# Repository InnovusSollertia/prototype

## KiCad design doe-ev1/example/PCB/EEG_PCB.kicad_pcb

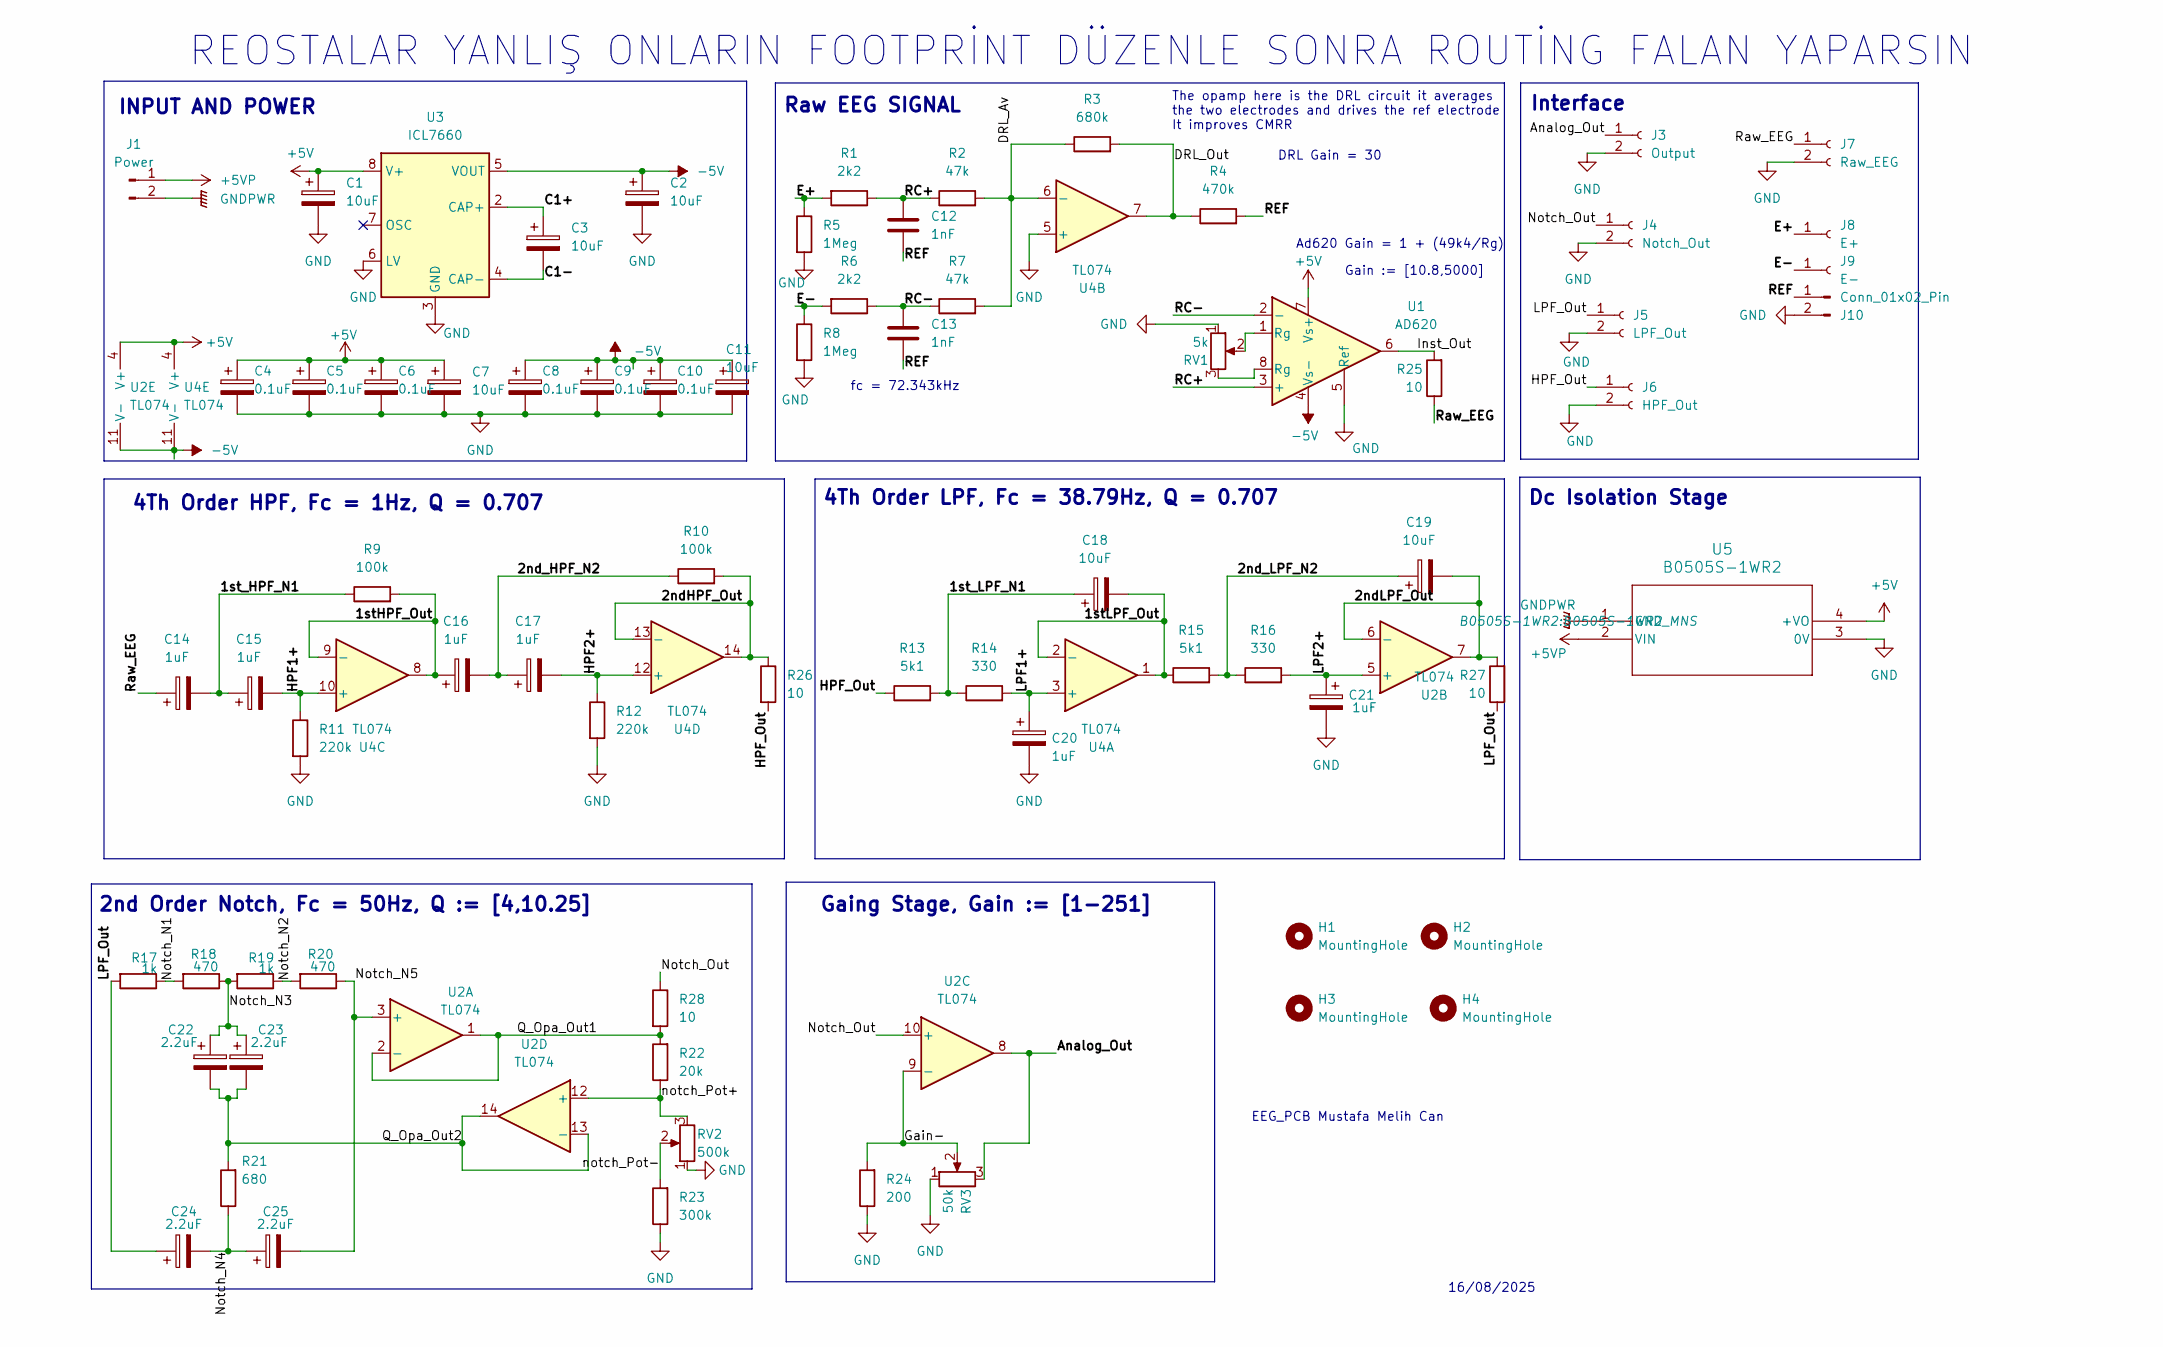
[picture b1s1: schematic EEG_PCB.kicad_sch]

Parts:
C1, C2, C3, C7, C11, C18, C19: 10uF; CP_Radial_D5.0mm_P2.50mm
C4, C5, C6, C8, C9, C10: 0.1uF; CP_Radial_D5.0mm_P2.50mm
C12, C13: 1nF; C_Disc_D4.7mm_W2.5mm_P5.00mm
C14, C15, C16, C17, C20, C21: 1uF; CP_Radial_D5.0mm_P2.50mm
C22, C23, C24, C25: 2.2uF; CP_Radial_D5.0mm_P2.50mm
H1, H2, H3, H4: MountingHole; MountingHole_4.3mm_M4
J1: Power; PinHeader_1x02_P2.54mm_Vertical
J3: Output; PinHeader_1x02_P2.54mm_Vertical
J4: Notch_Out; PinHeader_1x02_P2.54mm_Vertical
J5: LPF_Out; PinHeader_1x02_P2.54mm_Vertical
J6: HPF_Out; PinHeader_1x02_P2.54mm_Vertical
J7: Raw_EEG; PinHeader_1x02_P2.54mm_Vertical
J8: E+; PinHeader_1x01_P2.54mm_Vertical
J9: E-; PinHeader_1x01_P2.54mm_Vertical
J10: Conn_01x02_Pin; PinHeader_1x02_P2.54mm_Vertical
R1, R6: 2k2; R_Axial_DIN0207_L6.3mm_D2.5mm_P10.16mm_Horizontal
R2, R7: 47k; R_Axial_DIN0207_L6.3mm_D2.5mm_P10.16mm_Horizontal
R3: 680k; R_Axial_DIN0207_L6.3mm_D2.5mm_P10.16mm_Horizontal
R4: 470k; R_Axial_DIN0207_L6.3mm_D2.5mm_P10.16mm_Horizontal
R5, R8: 1Meg; R_Axial_DIN0207_L6.3mm_D2.5mm_P10.16mm_Horizontal
R9, R10: 100k; R_Axial_DIN0207_L6.3mm_D2.5mm_P10.16mm_Horizontal
R11, R12: 220k; R_Axial_DIN0207_L6.3mm_D2.5mm_P10.16mm_Horizontal
R13, R15: 5k1; R_Axial_DIN0207_L6.3mm_D2.5mm_P10.16mm_Horizontal
R14, R16: 330; R_Axial_DIN0207_L6.3mm_D2.5mm_P10.16mm_Horizontal
R17, R19: 1k; R_Axial_DIN0207_L6.3mm_D2.5mm_P10.16mm_Horizontal
R18, R20: 470; R_Axial_DIN0207_L6.3mm_D2.5mm_P10.16mm_Horizontal
R21: 680; R_Axial_DIN0207_L6.3mm_D2.5mm_P10.16mm_Horizontal
R22: 20k; R_Axial_DIN0207_L6.3mm_D2.5mm_P10.16mm_Horizontal
R23: 300k; R_Axial_DIN0207_L6.3mm_D2.5mm_P10.16mm_Horizontal
R24: 200; R_Axial_DIN0207_L6.3mm_D2.5mm_P10.16mm_Horizontal
R25, R26, R27, R28: 10; R_Axial_DIN0207_L6.3mm_D2.5mm_P10.16mm_Horizontal
RV1: 5k; Potentiometer_Alps_RK163_Single_Horizontal
RV2: 500k; Potentiometer_Alps_RK163_Single_Horizontal
RV3: 50k; Potentiometer_Alps_RK163_Single_Horizontal
U1: AD620; DIP-8_W7.62mm_LongPads
U2, U4: TL074; DIP-14_W7.62mm_LongPads
U3: ICL7660; DIP-8_W7.62mm_LongPads
U5: B0505S-1WR2; B0505S-1WR2_MNS

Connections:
+5V: C1.1, C4.1, C5.1, C6.1, C7.1, U1.7 (Vs+), U2.4 (V+), U3.8 (V+), U4.4 (V+), U5.4 (+VO)
+5VP: J1.1, U5.2 (VIN)
-5V: C2.1, C8.1, C9.1, C10.1, C11.1, U1.4 (Vs-), U2.11 (V-), U3.5 (VOUT), U4.11 (V-)
/1stHPF_Out: C16.1, R9.2, U4.8, U4.9 (-)
/1stLPF_Out: C18.2, R15.1, U4.1, U4.2 (-)
/1st_HPF_N1: C14.2, C15.1, R9.1
/1st_LPF_N1: C18.1, R13.2, R14.1
/2ndHPF_Out: R10.2, R26.1, U4.13 (-), U4.14
/2ndLPF_Out: C19.2, R27.2, U2.6 (-), U2.7
/2nd_HPF_N2: C16.2, C17.1, R10.1
/2nd_LPF_N2: C19.1, R15.2, R16.1
/Analog_Out: J3.1, RV3.3, U2.8
/C1+: C3.1, U3.2 (CAP+)
/C1-: C3.2, U3.4 (CAP-)
/DRL_Av: R2.2, R3.1, R7.2, U4.6 (-)
/DRL_Out: R3.2, R4.1, U4.7
/E+: J8.1, R1.2, R5.1
/E-: J9.1, R6.2, R8.1
/Gain-: R24.2, RV3.2, U2.9 (-)
/HPF1+: C15.2, R11.1, U4.10 (+)
/HPF2+: C17.2, R12.1, U4.12 (+)
/HPF_Out: J6.1, R13.1, R26.2
/Inst_Out: R25.2, U1.6
/LPF1+: C20.1, R14.2, U4.3 (+)
/LPF2+: C21.1, R16.2, U2.5 (+)
/LPF_Out: C24.1, J5.1, R17.2, R27.1
/Notch_N1: R17.1, R18.2
/Notch_N2: R19.1, R20.2
/Notch_N3: C22.1, C23.1, R18.1, R19.2
/Notch_N4: C24.2, C25.1, R21.1
/Notch_N5: C25.2, R20.1, U2.3 (+)
/Notch_Out: J4.1, R28.1, U2.10 (+)
/Q_Opa_Out1: R22.2, R28.2, U2.1, U2.2 (-)
/Q_Opa_Out2: C22.2, C23.2, R21.2, U2.13 (-), U2.14
/RC+: C12.1, R1.1, R2.1, U1.3 (+)
/RC-: C13.1, R6.1, R7.1, U1.2 (-)
/REF: C12.2, C13.2, J10.1, R4.2
/Raw_EEG: C14.1, J7.1, R25.1
/notch_Pot+: R22.1, RV2.3, U2.12 (+)
/notch_Pot-: R23.2, RV2.2
GND: C1.2, C2.2, C4.2, C5.2, C6.2, C7.2, C8.2, C9.2, C10.2, C11.2, C20.2, C21.2, J3.2, J4.2, J5.2, J6.2, J7.2, J10.2, R5.2, R8.2, R11.2, R12.2, R23.1, R24.1, RV1.1, RV2.1, RV3.1, U1.5 (Ref), U3.3 (GND), U3.6 (LV), U4.5 (+), U5.3 (0V)
GNDPWR: J1.2, U5.1 (GND)
unnamed: RV1.2, U1.1 (Rg)
unnamed: RV1.3, U1.8 (Rg)

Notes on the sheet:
REOSTALAR YANLIŞ ONLARIN FOOTPRİNT DÜZENLE SONRA ROUTİNG FALAN YAPARSIN
fc = 72.343kHz
The opamp here is the DRL circuit it averages the two electrodes and drives the ref electrode It improves CMRR
DRL Gain = 30
Interface
Ad620 Gain = 1 + (49k4/Rg)
Dc Isolation Stage
4Th Order LPF, Fc = 38.79Hz, Q = 0.707
2nd Order Notch, Fc = 50Hz, Q := [4,10.25]
4Th Order HPF, Fc = 1Hz, Q = 0.707
Gaing Stage, Gain := [1-251]
EEG_PCB Mustafa Melih Can
INPUT AND POWER
Raw EEG SIGNAL
Gain := [10.8,5000]
16/08/2025

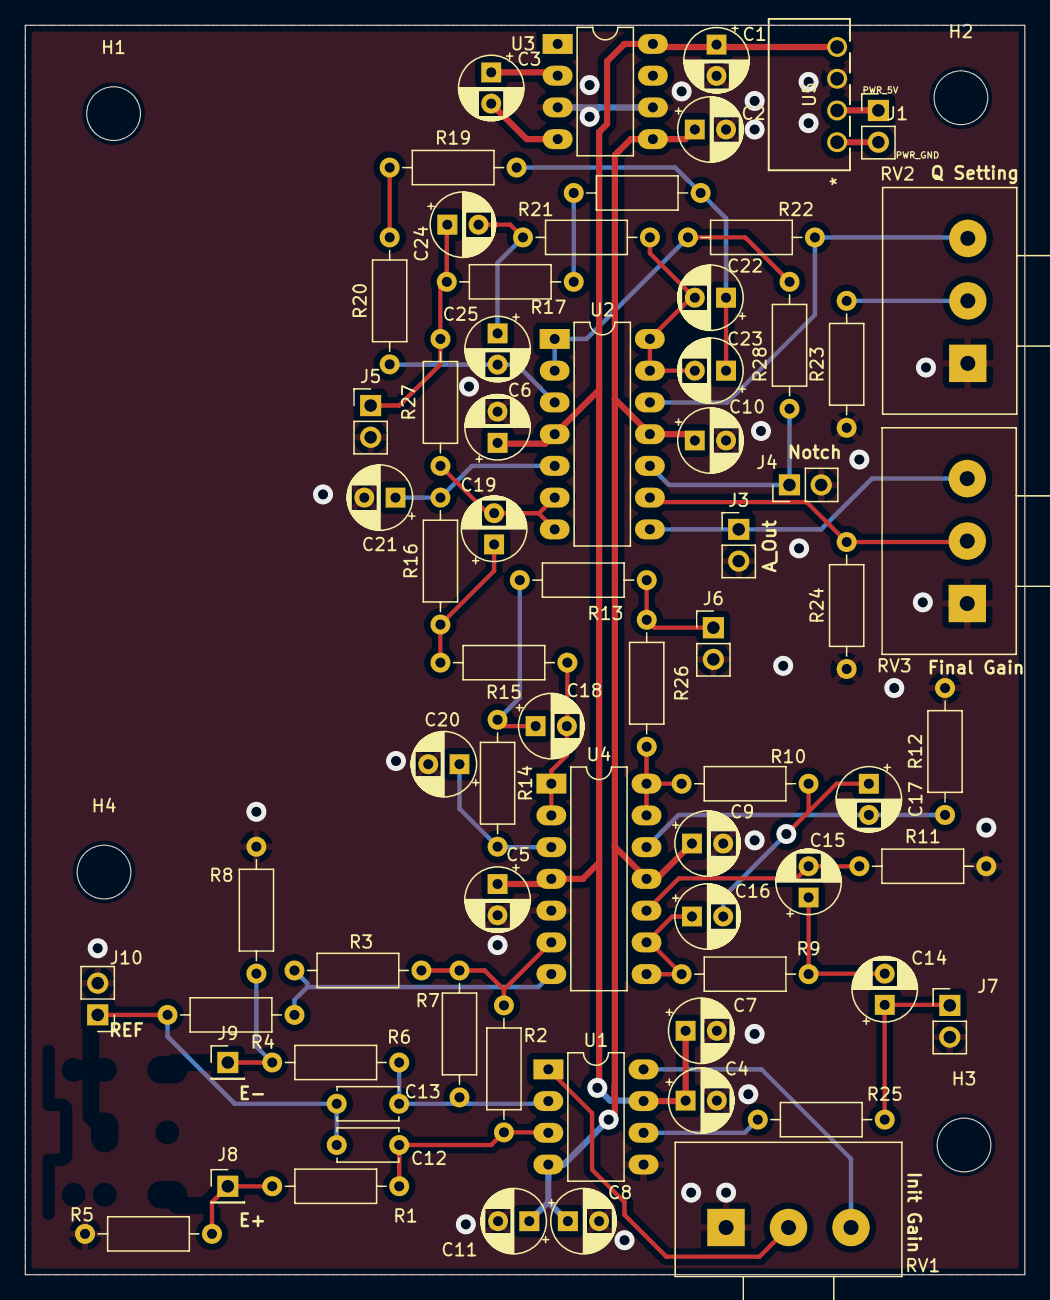
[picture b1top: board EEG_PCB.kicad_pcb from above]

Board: 2 copper layers, 80.0 x 100.0 mm, 74 parts (0 on the bottom side), 44 nets.

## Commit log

2026-01-02 20260102_1950
2026-01-02 20260102_2133
